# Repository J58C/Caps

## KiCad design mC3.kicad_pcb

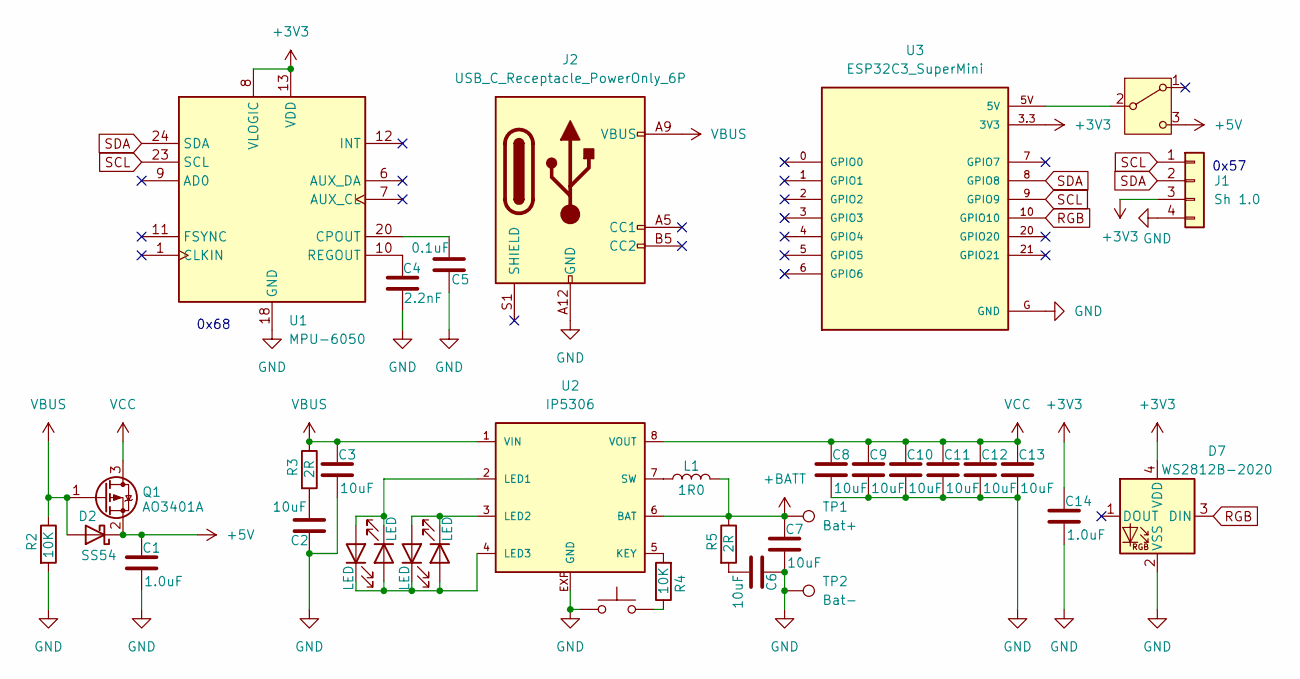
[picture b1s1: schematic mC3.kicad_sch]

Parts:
C1, C14: 1.0uF; C_0402_1005Metric
C2, C3, C6, C7, C8, C9, C10, C11, C12, C13: 10uF; C_0402_1005Metric
C4: 2.2nF; C_0603_1608Metric
C5: 0.1uF; C_0402_1005Metric
D2: SS54; D_SMA
D3, D4, D5, D6: LED; LED_0402_1005Metric
D7: WS2812B-2020; LED_WS2812B-2020_PLCC4_2.0x2.0mm
J1: Sh 1.0; JST_SH_BM04B-SRSS-TB_1x04-1MP_P1.00mm_Vertical
J2: USB_C_Receptacle_PowerOnly_6P; USB_C_Receptacle_GCT_USB4135-GF-A_6P_TopMnt_Horizontal
L1: 1R0; L_6.3x6.3_H3
Q1: AO3401A; SOT-23
R2, R4: 10K; R_0402_1005Metric
R3, R5: 2R; R_0402_1005Metric
SW1: SW_Push; SW_SPST_CK_KMS2xxGP
SW2: SW_SPDT; SW_SPDT_PCM12
TP1: Bat+; TestPoint_Pad_D1.5mm
TP2: Bat-; TestPoint_Pad_D1.5mm
U1: MPU-6050; InvenSense_QFN-24_4x4mm_P0.5mm_NoMask
U2: IP5306
U3: ESP32C3_SuperMini; ESP32C3_Supermini_SMD

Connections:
+3V3: C14.1, D7.4 (VDD), J1.3, U1.8 (VLOGIC), U1.13 (VDD), U3.3.3 (3V3)
+5V: C1.1, D2.1 (K), Q1.2 (S), SW2.3 (C)
+BATT: C7.1, L1.2, R5.1, TP1.1, U2.6 (BAT)
GND: C1.2, C2.1, C3.2, C4.1, C5.2, C6.1, C7.2, C8.2, C9.2, C10.2, C11.2, C12.2, C13.2, C14.2, D7.2 (VSS), J1.4, J2.A12 (GND), J2.B12 (GND), R2.2, SW1.2, TP2.1, U1.18 (GND), U2.EXP (GND), U3.G (GND)
unnamed: C2.2, R3.2
unnamed: C6.2, R5.2
unnamed: D3.2 (A), D4.1 (K), U2.2 (LED1)
unnamed: D3.1 (K), D4.2 (A), D5.1 (K), D6.2 (A), U2.4 (LED3)
unnamed: D5.2 (A), D6.1 (K), U2.3 (LED2)
unnamed: R4.1, SW1.1
unnamed: SW2.2 (B), U3.5V
unnamed: C5.1, U1.20 (CPOUT)
unnamed: C4.2, U1.10 (REGOUT)
unnamed: R4.2, U2.5 (KEY)
unnamed: L1.1, U2.7 (SW)
RGB: D7.3 (DIN), U3.10 (GPIO10)
SCL: J1.1, U1.23 (SCL), U3.9 (GPIO9)
SDA: J1.2, U1.24 (SDA), U3.8 (GPIO8)
VBUS: C3.1, D2.2 (A), J2.A9 (VBUS), J2.B9 (VBUS), Q1.1 (G), R2.1, R3.1, U2.1 (VIN)
VCC: C8.1, C9.1, C10.1, C11.1, C12.1, C13.1, Q1.3 (D), U2.8 (VOUT)

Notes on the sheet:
0x57
0x68

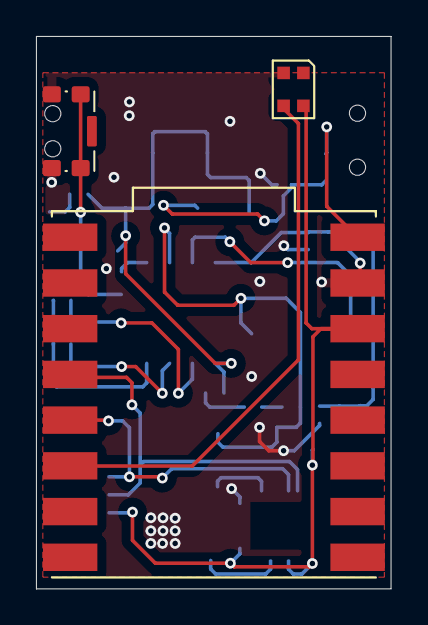
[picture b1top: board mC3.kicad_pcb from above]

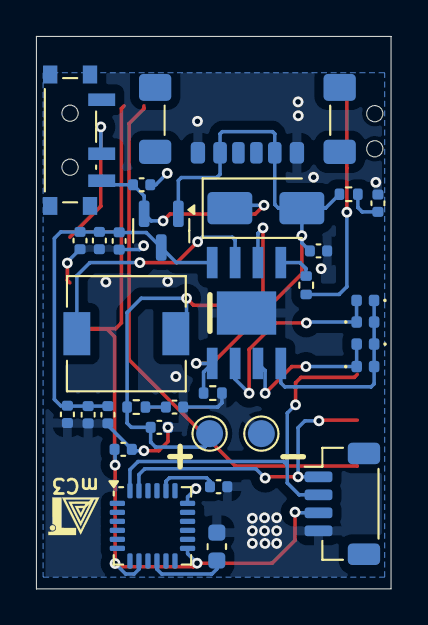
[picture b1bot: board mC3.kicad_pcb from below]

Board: 2 copper layers, 19.7 x 30.7 mm, 35 parts (32 on the bottom side), 20 nets.

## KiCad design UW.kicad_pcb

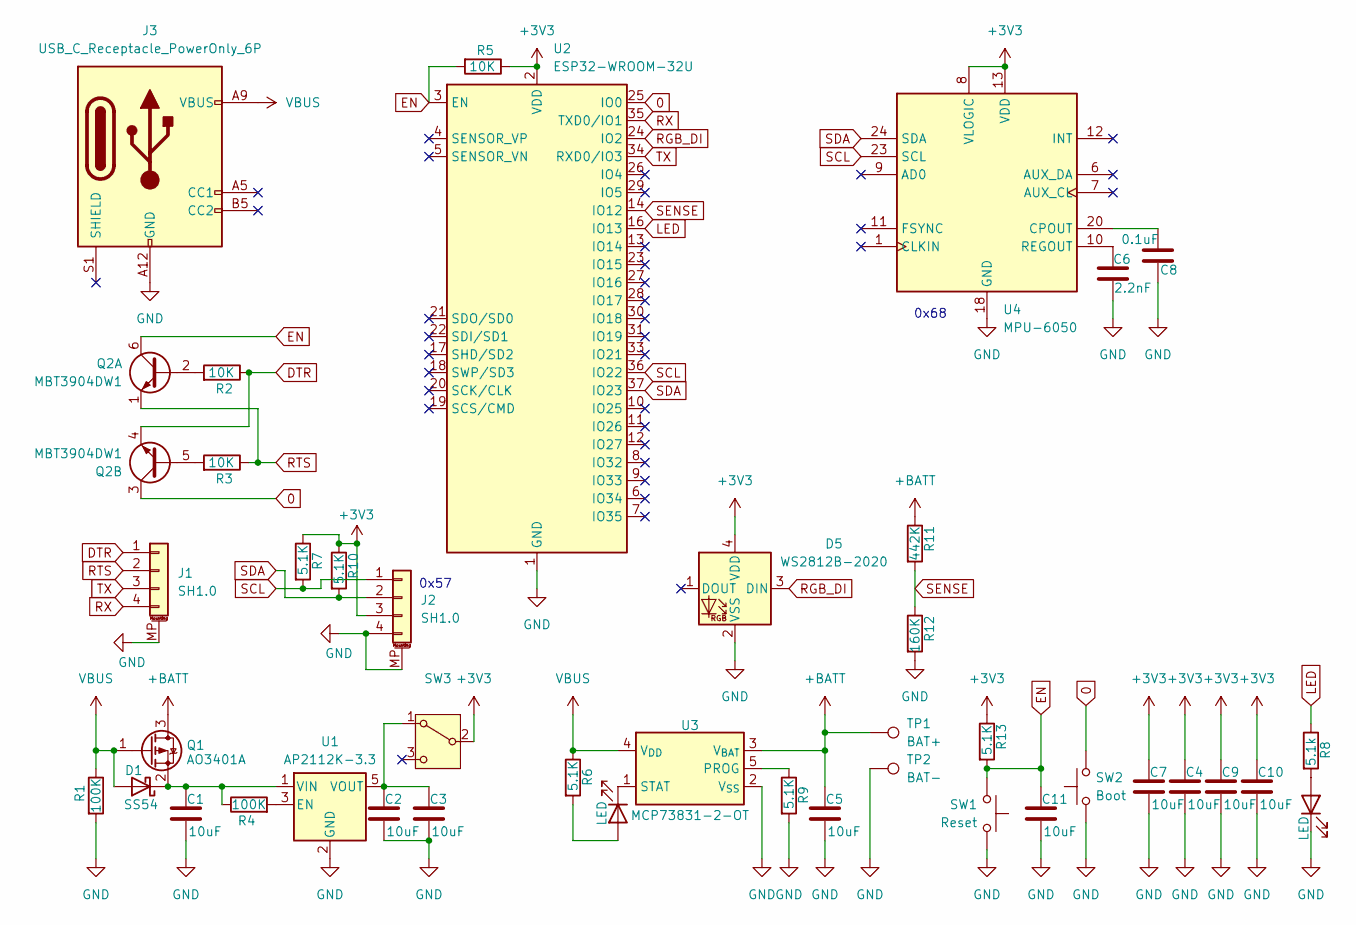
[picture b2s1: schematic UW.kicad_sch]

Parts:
C1, C2, C3, C4, C5, C7, C9, C10, C11: 10uF; C_0402_1005Metric
C6: 2.2nF; C_0603_1608Metric
C8: 0.1uF; C_0402_1005Metric
D1: SS54; D_SMA
D2, D4: LED; LED_0402_1005Metric
D5: WS2812B-2020; LED_WS2812B-2020_PLCC4_2.0x2.0mm
J1, J2: SH1.0; JST_SH_BM04B-SRSS-TB_1x04-1MP_P1.00mm_Vertical
J3: USB_C_Receptacle_PowerOnly_6P; USB_C_Receptacle_GCT_USB4135-GF-A_6P_TopMnt_Horizontal
Q1: AO3401A; SOT-23
Q2: MBT3904DW1; SOT-363_SC-70-6
R1, R4: 100K; R_0402_1005Metric
R2, R3, R5: 10K; R_0402_1005Metric
R6, R7, R9, R10, R13: 5.1K; R_0402_1005Metric
R8: 5.1k; R_0402_1005Metric
R11: 442K; R_0805_2012Metric
R12: 160K; R_0805_2012Metric
SW1: Reset; SW_Push_SPST_NO_Alps_SKRK
SW2: Boot; SW_Push_SPST_NO_Alps_SKRK
SW3: SW_SPDT; SW_SPDT_PCM12
TP1: BAT+; TestPoint_Pad_D1.5mm
TP2: BAT-; TestPoint_Pad_D1.5mm
U1: AP2112K-3.3; SOT-23-5
U2: ESP32-WROOM-32U
U3: MCP73831-2-OT; SOT-23-5
U4: MPU-6050; InvenSense_QFN-24_4x4mm_P0.5mm_NoMask

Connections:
0: Q2.3 (C2), SW2.2, U2.25 (IO0)
+3V3: C4.1, C7.1, C9.1, C10.1, D5.4 (VDD), J2.3, R5.1, R7.1, R10.1, R13.1, SW3.2 (B), U2.2 (VDD), U4.8 (VLOGIC), U4.13 (VDD)
+BATT: C5.1, Q1.3 (D), R11.1, TP1.1, U3.3 (V_{BAT})
DTR: J1.1, Q2.4 (E2), R2.1
EN: C11.1, Q2.6 (C1), R5.2, R13.2, SW1.2, U2.3 (EN)
GND: C1.2, C2.2, C3.2, C4.2, C5.2, C6.1, C7.2, C8.2, C9.2, C10.2, C11.2, D4.1 (K), D5.2 (VSS), J1.MP (MountPin), J2.4, J2.MP (MountPin), J3.A12 (GND), J3.B12 (GND), R1.2, R9.2, R12.2, SW1.1, SW2.1, TP2.1, U1.2 (GND), U2.1 (GND), U2.15 (GND), U2.38 (GND), U2.39 (GND), U3.2 (V_{SS}), U4.18 (GND)
LED: R8.1, U2.16 (IO13)
unnamed: C1.1, D1.1 (K), Q1.2 (S), R4.1, U1.1 (VIN)
unnamed: D2.2 (A), R6.2
unnamed: D2.1 (K), U3.1 (STAT)
unnamed: D4.2 (A), R8.2
unnamed: Q2.2 (B1), R2.2
unnamed: Q2.5 (B2), R3.2
unnamed: C2.1, C3.1, SW3.1 (A), U1.5 (VOUT)
unnamed: R4.2, U1.3 (EN)
unnamed: R9.1, U3.5 (PROG)
unnamed: C8.1, U4.20 (CPOUT)
unnamed: C6.2, U4.10 (REGOUT)
RGB_DI: D5.3 (DIN), U2.24 (IO2)
RTS: J1.2, Q2.1 (E1), R3.1
RX: J1.4, U2.35 (TXD0/IO1)
SCL: J2.1, R7.2, U2.36 (IO22), U4.23 (SCL)
SDA: J2.2, R10.2, U2.37 (IO23), U4.24 (SDA)
SENSE: R11.2, R12.1, U2.14 (IO12)
TX: J1.3, U2.34 (RXD0/IO3)
VBUS: D1.2 (A), J3.A9 (VBUS), J3.B9 (VBUS), Q1.1 (G), R1.1, R6.1, U3.4 (V_{DD})

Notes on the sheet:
0x57
0x68

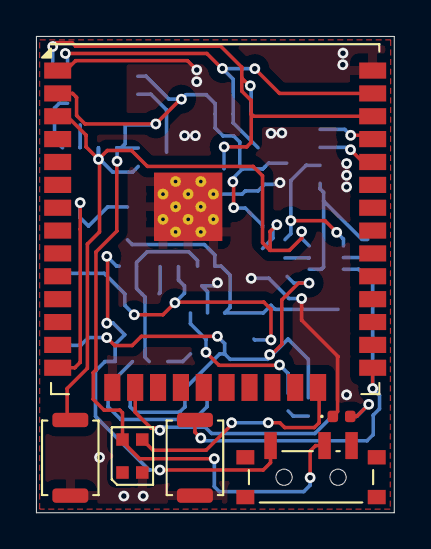
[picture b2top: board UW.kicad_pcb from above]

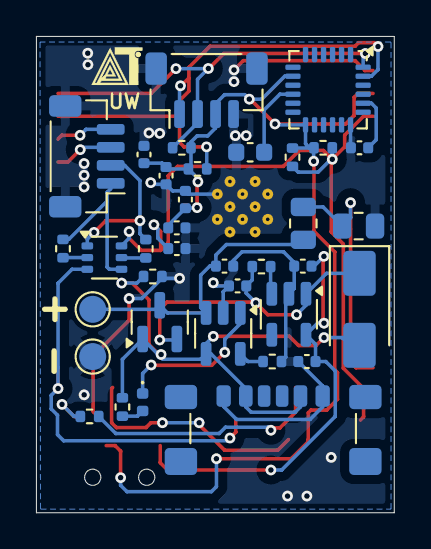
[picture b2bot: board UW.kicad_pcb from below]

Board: 2 copper layers, 19.9 x 26.5 mm, 42 parts (36 on the bottom side), 26 nets.

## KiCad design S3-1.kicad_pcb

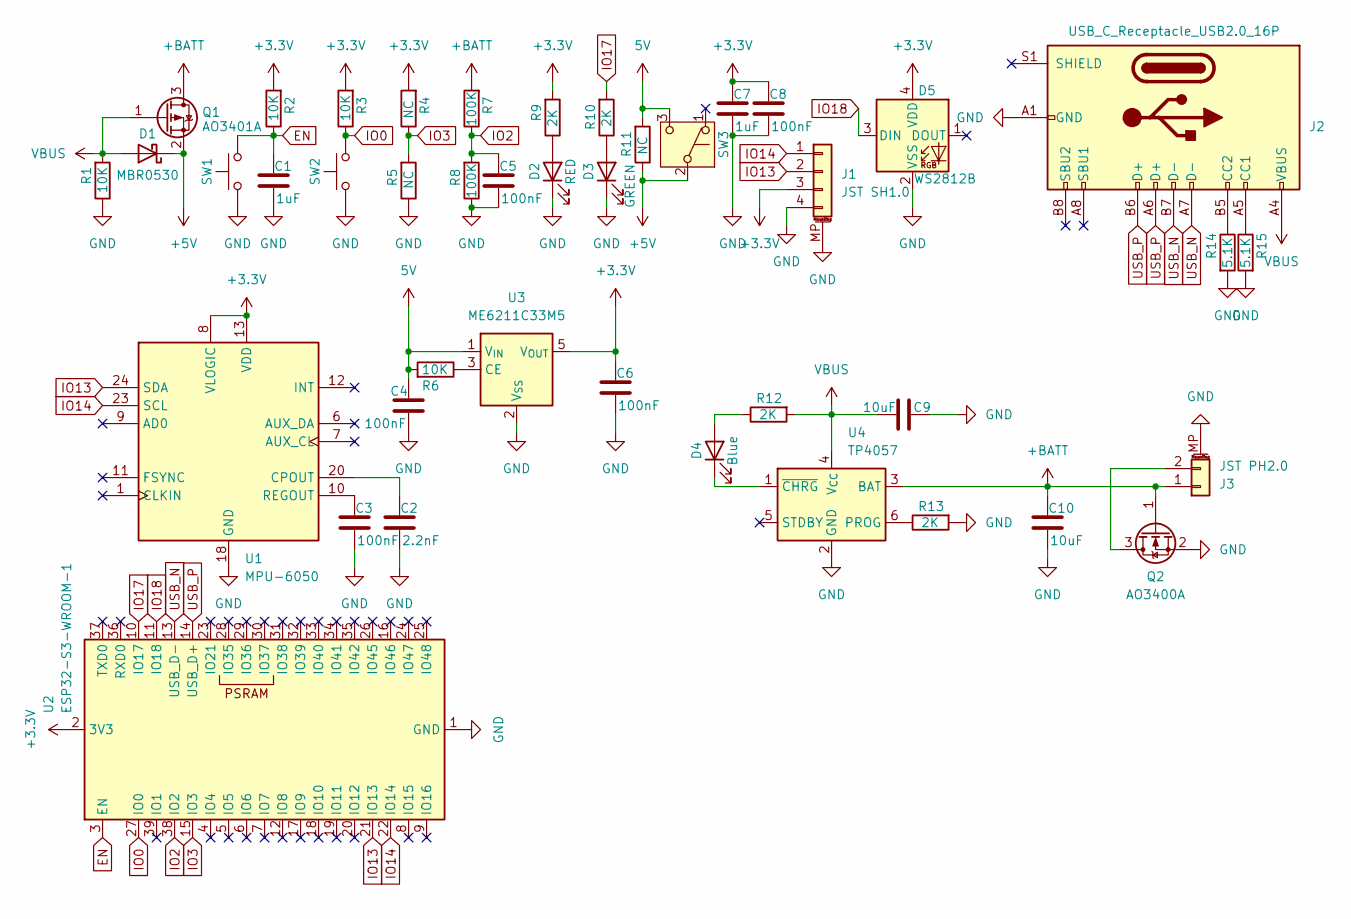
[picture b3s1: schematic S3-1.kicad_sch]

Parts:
C1, C7: 1uF; C_0402_1005Metric
C2: 2.2nF; C_0603_1608Metric
C3, C4, C5, C6, C8: 100nF; C_0402_1005Metric
C9, C10: 10uF; C_0402_1005Metric
D1: MBR0530; D_SOD-123
D2: RED; LED_0402_1005Metric
D3: GREEN; LED_0402_1005Metric
D4: Blue; LED_0402_1005Metric
D5: WS2812B; LED_WS2812B-2020_PLCC4_2.0x2.0mm
J1: JST SH1.0; JST_SH_BM04B-SRSS-TB_1x04-1MP_P1.00mm_Vertical
J2: USB_C_Receptacle_USB2.0_16P; USB_C_Receptacle_GCT_USB4110
J3: JST PH2.0; JST_PH_B2B-PH-SM4-TB_1x02-1MP_P2.00mm_Vertical
Q1: AO3401A; SOT-23
Q2: AO3400A; SOT-23
R1, R2, R3, R6: 10K; R_0402_1005Metric
R4, R5, R11: NC; R_0402_1005Metric
R7, R8: 100K; R_0402_1005Metric
R9, R10, R12, R13: 2K; R_0402_1005Metric
R14, R15: 5.1K; R_0402_1005Metric
SW1, SW2: SW_Push; SW_Push_SPST_NO_Alps_SKRK
SW3: SW_Push_SPDT; SW_SPDT_PCM12
U1: MPU-6050; InvenSense_QFN-24_4x4mm_P0.5mm
U2: ESP32-S3-WROOM-1
U3: ME6211C33M5; SOT-23-5
U4: TP4057; TSOT-23-6

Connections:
5V: C4.1, R6.2, R11.2, SW3.3 (C), U3.1 (V_{IN})
+3.3V: C6.1, C7.1, C8.1, D5.4 (VDD), J1.3, R2.2, R3.2, R4.2, R9.2, U1.8 (VLOGIC), U1.13 (VDD), U2.2 (3V3), U3.5 (V_{OUT})
+5V: D1.1 (K), Q1.2 (S), R11.1, SW3.2 (B)
+BATT: C10.1, J3.1, Q1.3 (D), Q2.1 (G), R7.2, U4.3 (BAT)
EN: C1.1, R2.1, SW1.2, U2.3 (EN)
GND: C1.2, C2.2, C3.2, C4.2, C5.2, C6.2, C7.2, C8.2, C9.1, C10.2, D2.1 (K), D3.1 (K), D5.2 (VSS), J1.4, J1.MP (MountPin), J2.A1 (GND), J2.A12 (GND), J2.B1 (GND), J2.B12 (GND), J3.MP (MountPin), Q2.2 (S), R1.1, R5.1, R8.1, R13.2, R14.2, R15.2, SW1.1, SW2.1, U1.18 (GND), U2.1 (GND), U2.40 (GND), U2.41 (GND), U3.2 (V_{SS}), U4.2 (GND)
IO0: R3.1, SW2.2, U2.27 (IO0)
IO2: C5.1, R7.1, R8.2, U2.38 (IO2)
IO3: R4.1, R5.2, U2.15 (IO3)
IO13: J1.2, U1.24 (SDA), U2.21 (IO13)
IO14: J1.1, U1.23 (SCL), U2.22 (IO14)
IO17: R10.2, U2.10 (IO17)
IO18: D5.3 (DIN), U2.11 (IO18)
unnamed: D2.2 (A), R9.1
unnamed: D3.2 (A), R10.1
unnamed: D4.2 (A), R12.1
unnamed: D4.1 (K), U4.1 (~CHRG)
unnamed: J2.A5 (CC1), R15.1
unnamed: J2.B5 (CC2), R14.1
unnamed: J3.2, Q2.3 (D)
unnamed: C2.1, U1.20 (CPOUT)
unnamed: C3.1, U1.10 (REGOUT)
unnamed: R6.1, U3.3 (CE)
unnamed: R13.1, U4.6 (PROG)
USB_N: J2.A7 (D-), J2.B7 (D-), U2.13 (USB_D-)
USB_P: J2.A6 (D+), J2.B6 (D+), U2.14 (USB_D+)
VBUS: C9.2, D1.2 (A), J2.A4 (VBUS), J2.A9 (VBUS), J2.B4 (VBUS), J2.B9 (VBUS), Q1.1 (G), R1.2, R12.2, U4.4 (V_{CC})

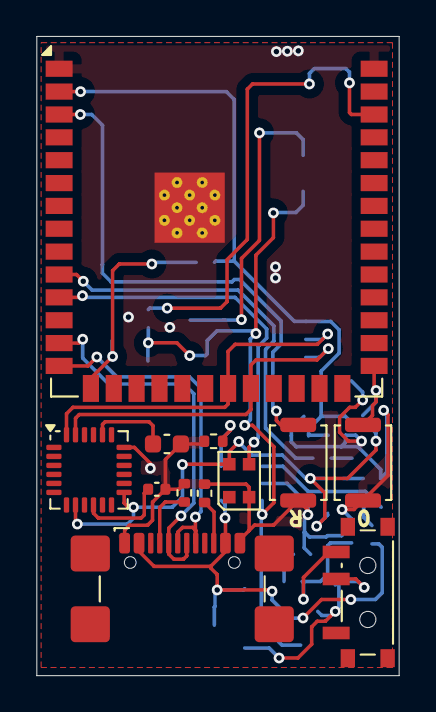
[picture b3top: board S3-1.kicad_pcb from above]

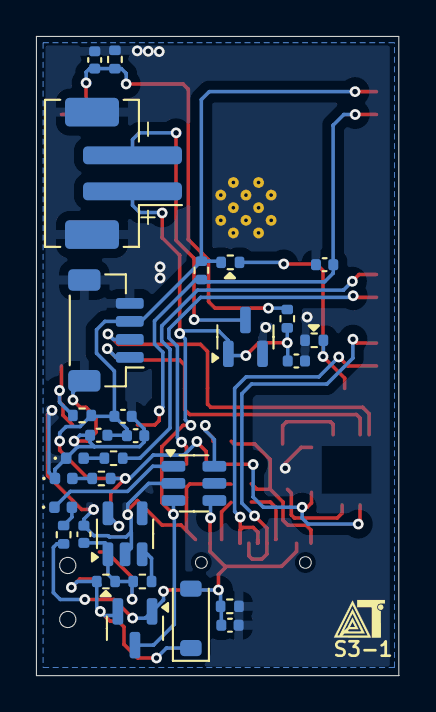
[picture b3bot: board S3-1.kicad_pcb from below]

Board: 2 copper layers, 20.1 x 35.5 mm, 42 parts (30 on the bottom side), 27 nets.

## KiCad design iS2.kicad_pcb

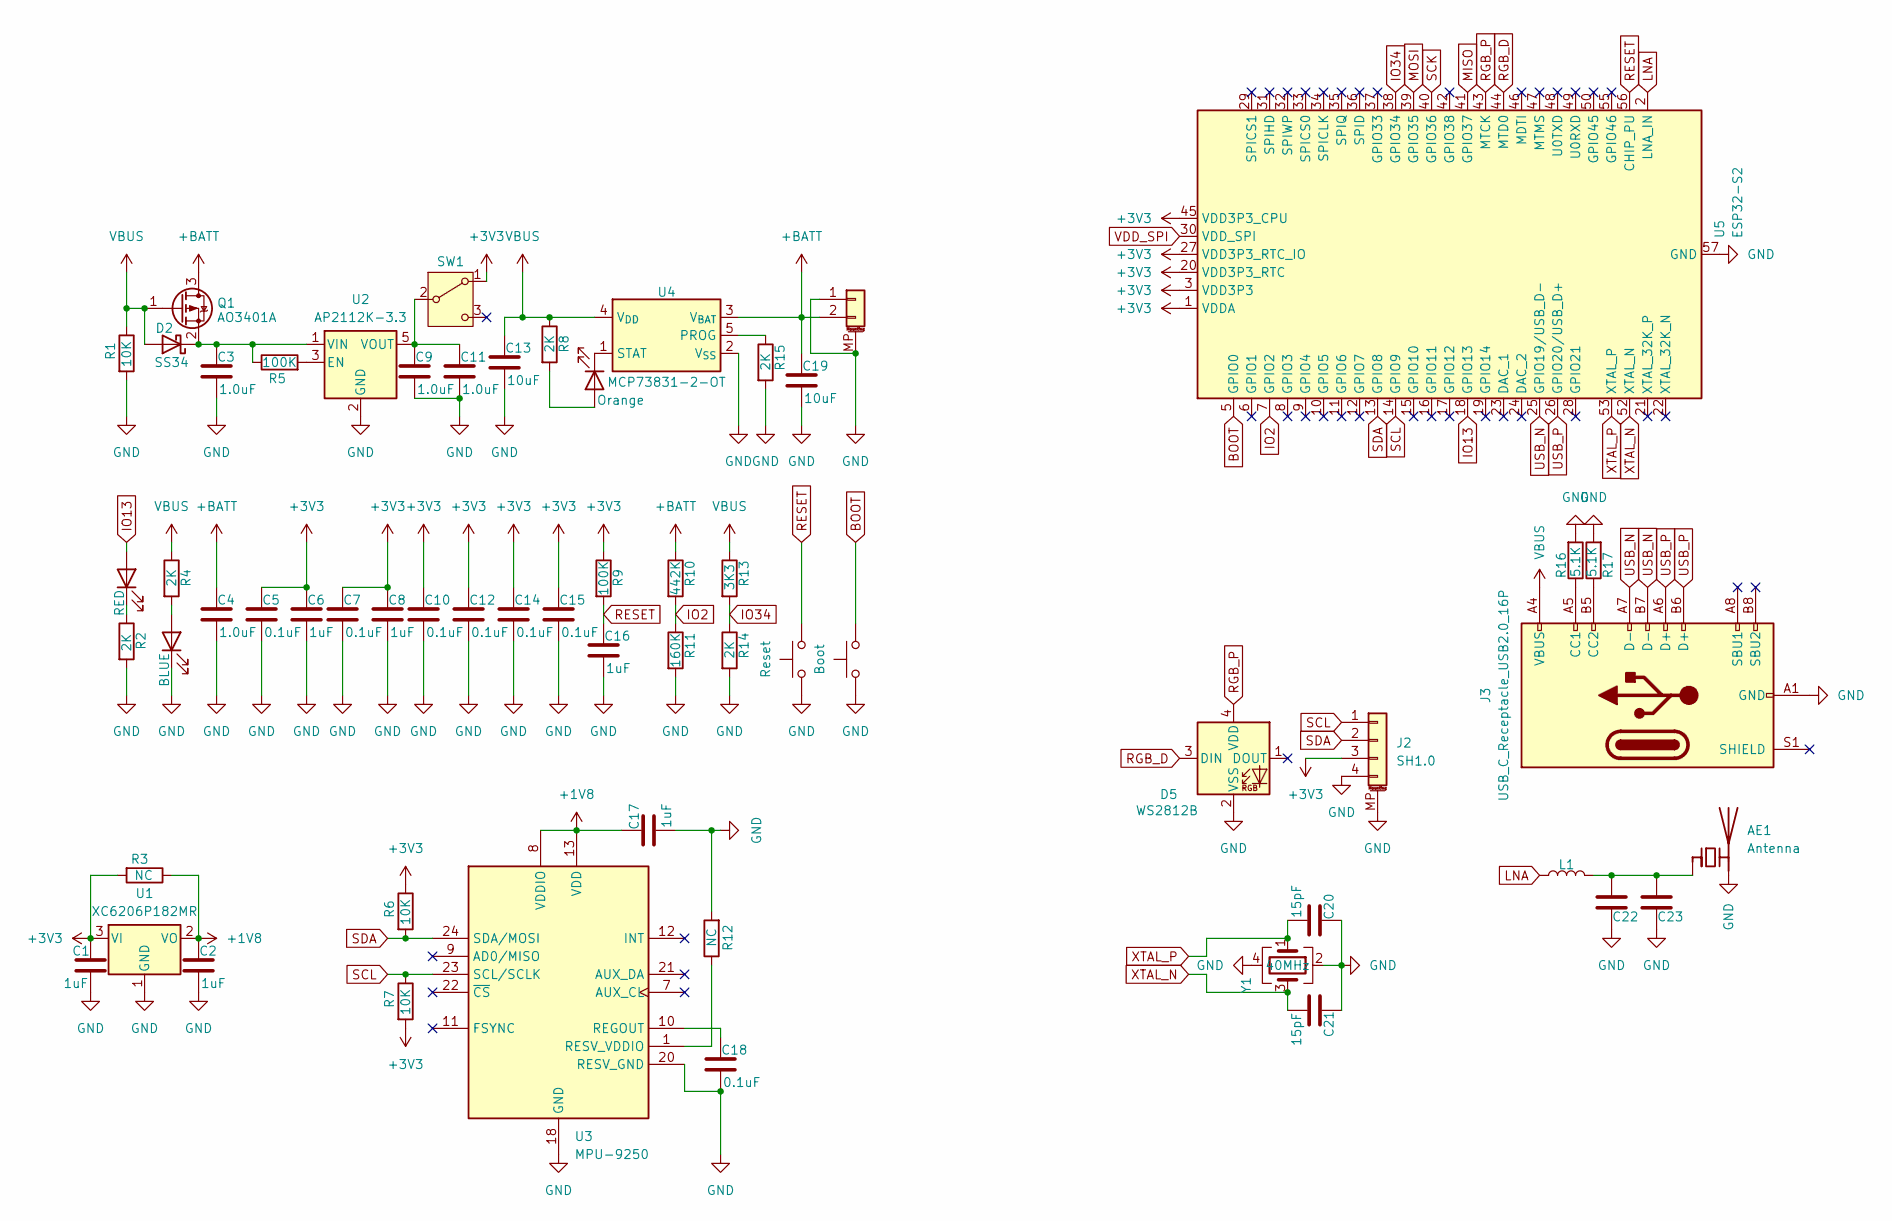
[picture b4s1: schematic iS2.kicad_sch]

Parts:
AE1: Antenna; Texas_SWRA117D_2.4GHz_Right
C1, C2, C6, C8, C16, C17, C23: 1uF; C_0402_1005Metric
C3, C4, C9, C11: 1.0uF; C_0402_1005Metric
C5, C7, C10, C12, C14, C15, C18, C22: 0.1uF; C_0402_1005Metric
C13, C19: 10uF; C_0402_1005Metric
C20, C21: 15pF; C_0402_1005Metric
D1: RED; LED_0402_1005Metric
D2: SS34; D_SMA
D3: BLUE; LED_0402_1005Metric
D4: Orange; LED_0402_1005Metric
D5: WS2812B; LED_WS2812B-2020_PLCC4_2.0x2.0mm
J1: Conn_01x02_MountingPin; JST_PH_B2B-PH-SM4-TB_1x02-1MP_P2.00mm_Vertical
J2: SH1.0; JST_SH_BM04B-SRSS-TB_1x04-1MP_P1.00mm_Vertical
J3: USB_C_Receptacle_USB2.0_16P; USB_C_Receptacle_GCT_USB4110
L1: L_0805_2012Metric
Q1: AO3401A; SOT-23
R1, R6, R7: 10K; R_0402_1005Metric
R2, R4, R8, R14, R15: 2K; R_0402_1005Metric
R3, R12: NC; R_0402_1005Metric
R5, R9: 100K; R_0402_1005Metric
R10: 442K; R_0805_2012Metric
R11: 160K; R_0805_2012Metric
R13: 3K3; R_0402_1005Metric
R16, R17: 5.1K; R_0402_1005Metric
SW1: SW_SPDT; SW_SPDT_PCM12
SW2: Reset; SW_SPST_B3U-1000P
SW3: Boot; SW_SPST_B3U-1000P
U1: XC6206P182MR; SOT-23-3
U2: AP2112K-3.3; SOT-23-5
U3: MPU-9250; InvenSense_QFN-24_3x3mm_P0.4mm
U4: MCP73831-2-OT; SOT-23-5
U5: ESP32-S2; QFN-56-1EP_7x7mm_P0.4mm_EP4x4mm
Y1: 40MHz; Crystal_SMD_3225-4Pin_3.2x2.5mm

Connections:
+1V8: C2.1, C17.1, R3.1, U1.2 (VO), U3.8 (VDDIO), U3.13 (VDD)
+3V3: C1.1, C5.1, C6.1, C7.1, C8.1, C10.1, C12.1, C14.1, C15.1, J2.3, R3.2, R6.1, R7.2, R9.1, SW1.1 (A), U1.3 (VI), U5.1 (VDDA), U5.3 (VDD3P3), U5.4 (VDD3P3), U5.20 (VDD3P3_RTC), U5.27 (VDD3P3_RTC_IO), U5.45 (VDD3P3_CPU), U5.51 (VDDA), U5.54 (VDDA)
+BATT: C4.1, C19.1, J1.2, Q1.3 (D), R10.1, U4.3 (V_{BAT})
BOOT: SW3.2, U5.5 (GPIO0)
GND: AE1.2 (PCB_Trace), C1.2, C2.2, C3.2, C4.2, C5.2, C6.2, C7.2, C8.2, C9.2, C10.2, C11.2, C12.2, C13.2, C14.2, C15.2, C16.2, C17.2, C18.2, C19.2, C20.1, C21.1, C22.1, C23.1, D3.1 (K), D5.2 (VSS), J1.1, J1.MP (MountPin), J2.4, J2.MP (MountPin), J3.A1 (GND), J3.A12 (GND), J3.B1 (GND), J3.B12 (GND), R1.2, R2.2, R11.2, R12.2, R14.2, R15.2, R16.2, R17.2, SW2.1, SW3.1, U1.1 (GND), U2.2 (GND), U3.18 (GND), U3.20 (RESV_GND), U4.2 (V_{SS}), U5.57 (GND), Y1.2, Y1.4
IO2: R10.2, R11.1, U5.7 (GPIO2)
IO13: D1.2 (A), U5.18 (GPIO13)
IO34: R13.2, R14.1, U5.38 (GPIO34)
LNA: L1.1, U5.2 (LNA_IN)
MISO: U5.41 (GPIO37)
MOSI: U5.39 (GPIO35)
unnamed: AE1.1 (FEED), C22.2, C23.2, L1.2
unnamed: D1.1 (K), R2.1
unnamed: C3.1, D2.1 (K), Q1.2 (S), R5.1, U2.1 (VIN)
unnamed: D3.2 (A), R4.2
unnamed: D4.2 (A), R8.2
unnamed: D4.1 (K), U4.1 (STAT)
unnamed: J3.A5 (CC1), R16.1
unnamed: J3.B5 (CC2), R17.1
unnamed: C9.1, C11.1, SW1.2 (B), U2.5 (VOUT)
unnamed: R5.2, U2.3 (EN)
unnamed: C18.1, U3.10 (REGOUT)
unnamed: R12.1, U3.1 (RESV_VDDIO)
unnamed: R15.1, U4.5 (PROG)
RESET: C16.1, R9.2, SW2.2, U5.56 (CHIP_PU)
RGB_D: D5.3 (DIN), U5.44 (MTD0)
RGB_P: D5.4 (VDD), U5.43 (MTCK)
SCK: U5.40 (GPIO36)
SCL: J2.1, R7.1, U3.23 (SCL/SCLK), U5.14 (GPIO9)
SDA: J2.2, R6.2, U3.24 (SDA/MOSI), U5.13 (GPIO8)
USB_N: J3.A7 (D-), J3.B7 (D-), U5.25 (GPIO19/USB_D-)
USB_P: J3.A6 (D+), J3.B6 (D+), U5.26 (GPIO20/USB_D+)
VBUS: C13.1, D2.2 (A), J3.A4 (VBUS), J3.A9 (VBUS), J3.B4 (VBUS), J3.B9 (VBUS), Q1.1 (G), R1.1, R4.1, R8.1, R13.1, U4.4 (V_{DD})
VDD_SPI: U5.30 (VDD_SPI)
XTAL_N: C21.2, U5.52 (XTAL_N), Y1.3
XTAL_P: C20.2, U5.53 (XTAL_P), Y1.1

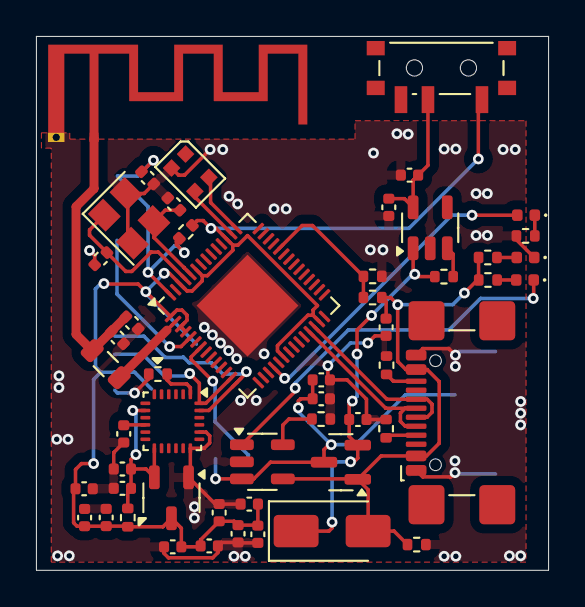
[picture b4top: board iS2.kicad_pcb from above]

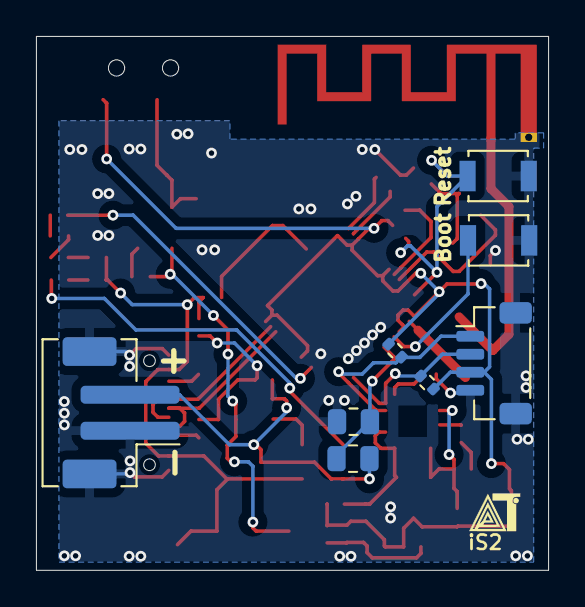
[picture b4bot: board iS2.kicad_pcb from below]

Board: 2 copper layers, 28.5 x 29.7 mm, 60 parts (8 on the bottom side), 32 nets.

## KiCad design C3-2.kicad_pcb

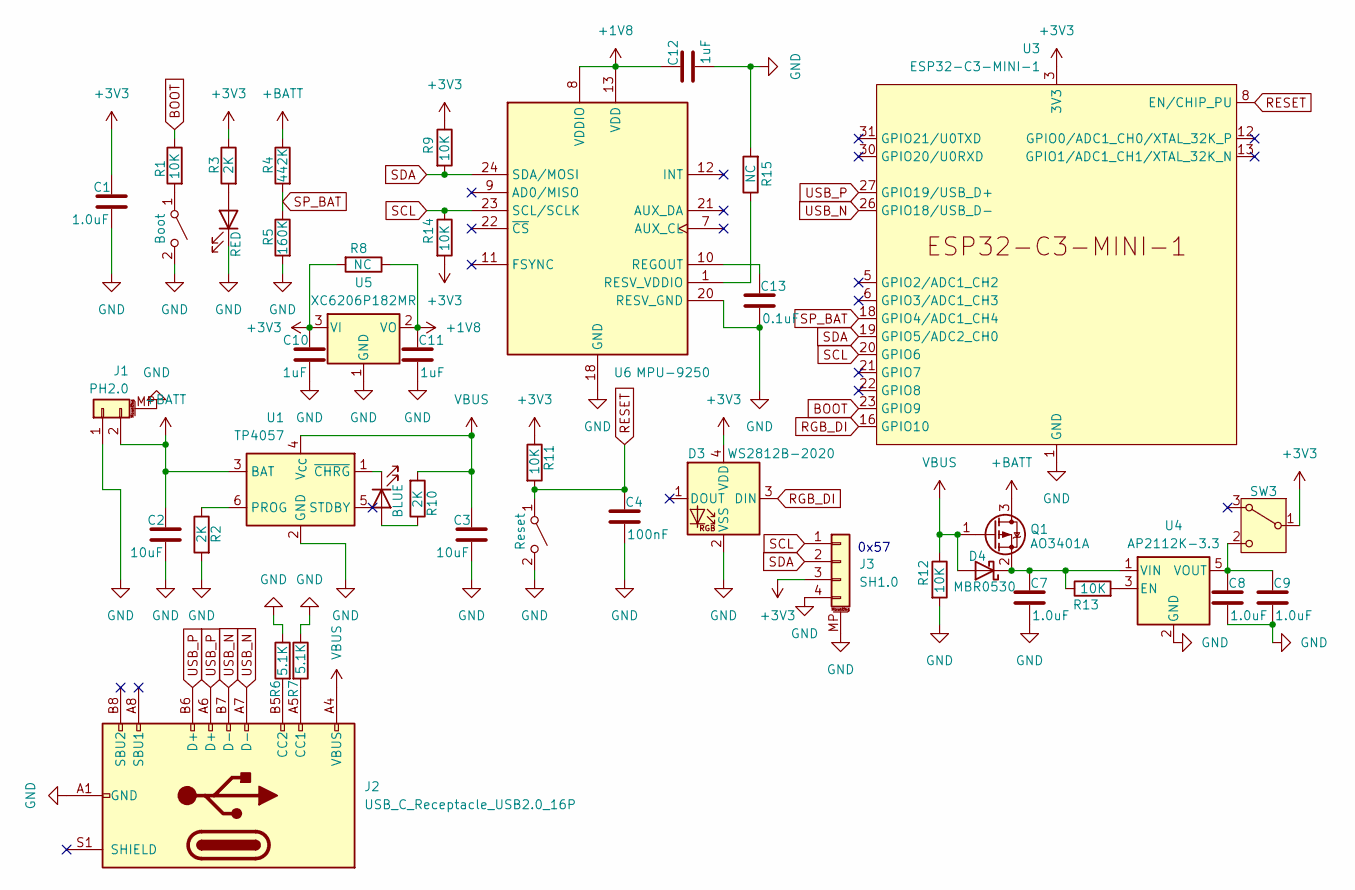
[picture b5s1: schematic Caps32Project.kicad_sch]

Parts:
C1, C7, C8, C9: 1.0uF; C_0402_1005Metric
C2, C3: 10uF; C_0402_1005Metric
C4: 100nF; C_0402_1005Metric
C10, C11, C12: 1uF; C_0402_1005Metric
C13: 0.1uF; C_0402_1005Metric
D1: RED; LED_0402_1005Metric
D2: BLUE; LED_0402_1005Metric
D3: WS2812B-2020; LED_WS2812B-2020_PLCC4_2.0x2.0mm
D4: MBR0530; D_SOD-123
J1: PH2.0; JST_PH_B2B-PH-SM4-TB_1x02-1MP_P2.00mm_Vertical
J2: USB_C_Receptacle_USB2.0_16P; USB_C_Receptacle_GCT_USB4110
J3: SH1.0; JST_SH_BM04B-SRSS-TB_1x04-1MP_P1.00mm_Vertical
Q1: AO3401A; SOT-23
R1, R9, R11, R12, R13, R14: 10K; R_0402_1005Metric
R2, R3, R10: 2K; R_0402_1005Metric
R4: 442K; R_0805_2012Metric
R5: 160K; R_0805_2012Metric
R6, R7: 5.1K; R_0402_1005Metric
R8, R15: NC; R_0402_1005Metric
SW1: Boot; SW_Push_SPST_NO_Alps_SKRK
SW2: Reset; SW_Push_SPST_NO_Alps_SKRK
SW3: SW_SPDT_312; SW_SPDT_PCM12
U1: TP4057; TSOT-23-6
U3: ESP32-C3-MINI-1
U4: AP2112K-3.3; SOT-23-5
U5: XC6206P182MR; SOT-23-3
U6: MPU-9250; InvenSense_QFN-24_3x3mm_P0.4mm

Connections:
+1V8: C11.1, C12.1, R8.1, U5.2 (VO), U6.8 (VDDIO), U6.13 (VDD)
+3V3: C1.1, C10.1, D3.4 (VDD), J3.3, R3.1, R8.2, R9.1, R11.1, R14.2, SW3.1 (B), U3.3 (3V3), U5.3 (VI)
+BATT: C2.1, J1.2, Q1.3 (D), R4.1, U1.3 (BAT)
BOOT: R1.1, U3.23 (GPIO9)
GND: C1.2, C2.2, C3.2, C4.2, C7.2, C8.2, C9.2, C10.2, C11.2, C12.2, C13.2, D1.1 (K), D3.2 (VSS), J1.1, J1.MP (MountPin), J2.A1 (GND), J2.A12 (GND), J2.B1 (GND), J2.B12 (GND), J3.4, J3.MP (MountPin), R2.2, R5.2, R6.1, R7.1, R12.2, R15.2, SW1.2 (B), SW2.2 (B), U1.2 (GND), U3.1 (GND), U3.2 (GND), U3.11 (GND), U3.14 (GND), U3.36 (GND), U3.37 (GND), U3.38 (GND), U3.39 (GND), U3.40 (GND), U3.41 (GND), U3.42 (GND), U3.43 (GND), U3.44 (GND), U3.45 (GND), U3.46 (GND), U3.47 (GND), U3.48 (GND), U3.49 (GND), U3.50 (GND), U3.51 (GND), U3.52 (GND), U3.53 (GND), U4.2 (GND), U5.1 (GND), U6.18 (GND), U6.20 (RESV_GND)
unnamed: D1.2 (A), R3.2
unnamed: D2.2 (A), R10.1
unnamed: D2.1 (K), U1.1 (~CHRG)
unnamed: C7.1, D4.1 (K), Q1.2 (S), R13.1, U4.1 (VIN)
unnamed: J2.A5 (CC1), R7.2
unnamed: J2.B5 (CC2), R6.2
unnamed: R1.2, SW1.1 (A)
unnamed: C8.1, C9.1, SW3.2 (C), U4.5 (VOUT)
unnamed: R2.1, U1.6 (PROG)
unnamed: R13.2, U4.3 (EN)
unnamed: C13.1, U6.10 (REGOUT)
unnamed: R15.1, U6.1 (RESV_VDDIO)
RESET: C4.1, R11.2, SW2.1 (A), U3.8 (EN/CHIP_PU)
RGB_DI: D3.3 (DIN), U3.16 (GPIO10)
SCL: J3.1, R14.1, U3.20 (GPIO6), U6.23 (SCL/SCLK)
SDA: J3.2, R9.2, U3.19 (GPIO5/ADC2_CH0), U6.24 (SDA/MOSI)
SP_BAT: R4.2, R5.1, U3.18 (GPIO4/ADC1_CH4)
USB_N: J2.A7 (D-), J2.B7 (D-), U3.26 (GPIO18/USB_D-)
USB_P: J2.A6 (D+), J2.B6 (D+), U3.27 (GPIO19/USB_D+)
VBUS: C3.1, D4.2 (A), J2.A4 (VBUS), J2.A9 (VBUS), J2.B4 (VBUS), J2.B9 (VBUS), Q1.1 (G), R10.2, R12.1, U1.4 (V_{CC})

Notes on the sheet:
0x57

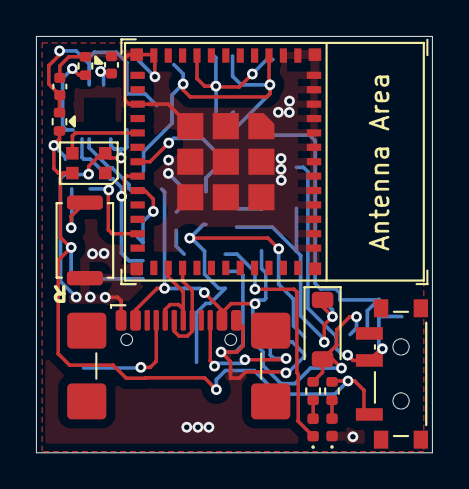
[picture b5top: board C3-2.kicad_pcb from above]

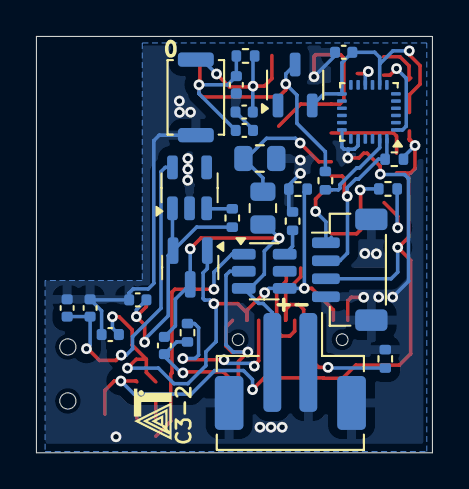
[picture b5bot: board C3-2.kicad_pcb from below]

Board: 2 copper layers, 22.0 x 23.1 mm, 42 parts (28 on the bottom side), 25 nets.

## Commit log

2025-01-29 Inital commit
2025-01-29 Intial file
2025-01-29 Inital file
2025-01-29 Update PCB render images
2025-01-30 Fix compress.yaml
2025-01-30 fix: compress workflow
2025-01-30 update compress
2025-01-30 add compress
2025-01-30 deleted
2025-01-30 deleted: Caps32Project.kicad_pcb
2025-01-30 fix error kicad
2025-01-30 check
2025-01-30 Remove images folder after moving to main
2025-01-30 testing
2025-01-30 shit
2025-01-31 Updates compress.yaml
2025-01-31 Updates workflows
2025-01-31 Update workflow
2025-01-31 test
2025-02-01 Update Board
2025-02-02 Drop
2025-02-04 Update sch
2025-02-11 Board Update
